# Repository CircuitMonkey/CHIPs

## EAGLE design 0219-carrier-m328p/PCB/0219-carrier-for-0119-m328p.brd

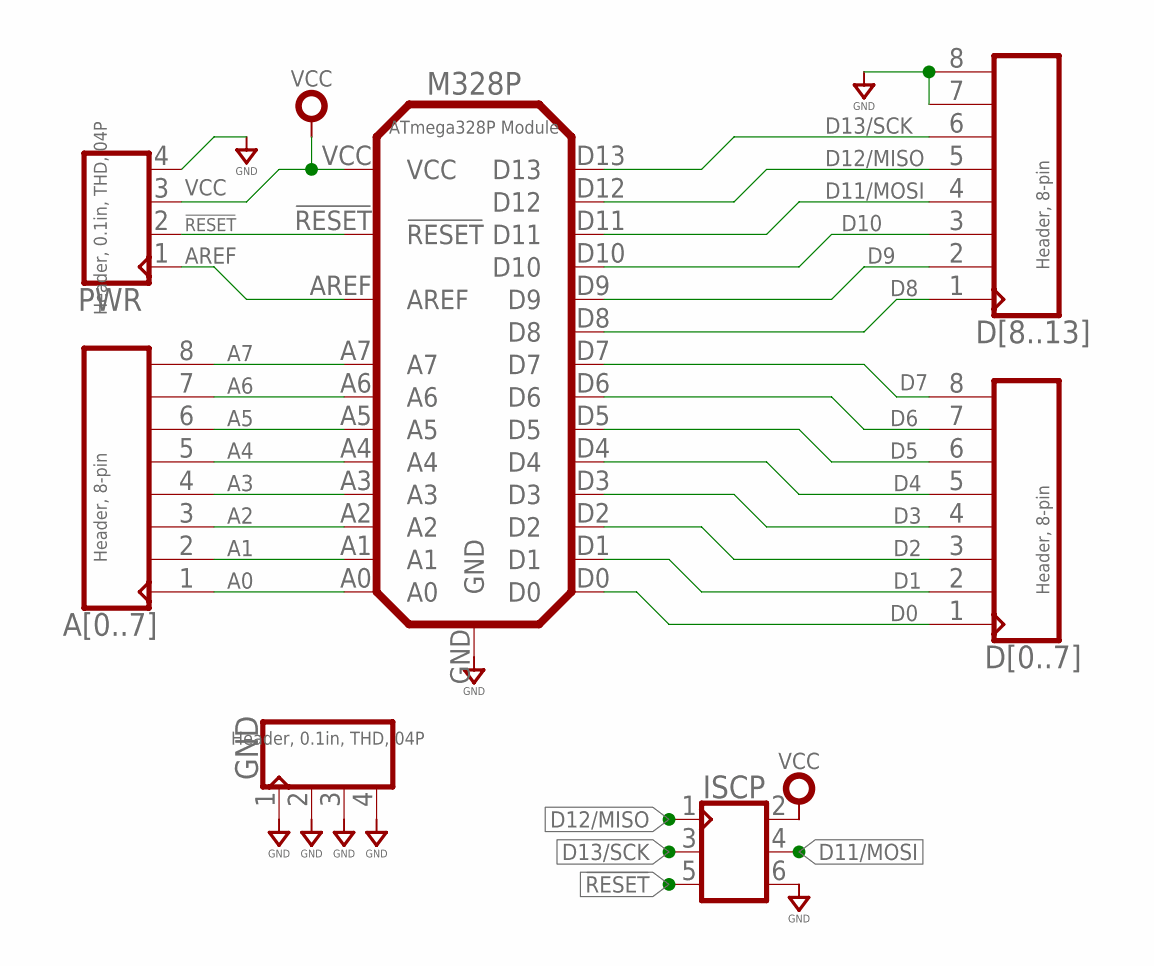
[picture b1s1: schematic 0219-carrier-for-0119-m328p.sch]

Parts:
A[0..7]: Header, 8-pin; MA08X1-VT-THD
D[0..7], D[8..13]: Header, 8-pin; MA08X1-VT-THD
GND: Header, 0.1in, THD, 04P; MA04X1-VT-THD
ISCP: CON_03X2-VT_SMD; MA03X2-VT-SMD
M328P: ATmega328P Module; 0119A
PWR: Header, 0.1in, THD, 04P; MA04X1-VT-THD

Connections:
!RESET: ISCP.5, M328P.!RESET, PWR.2
A0: A[0..7].1, M328P.A0
A1: A[0..7].2, M328P.A1
A2: A[0..7].3, M328P.A2
A3: A[0..7].4, M328P.A3
A4: A[0..7].5, M328P.A4
A5: A[0..7].6, M328P.A5
A6: A[0..7].7, M328P.A6
A7: A[0..7].8, M328P.A7
AREF: M328P.AREF, PWR.1
D0: D[0..7].1, M328P.D0
D1: D[0..7].2, M328P.D1
D2: D[0..7].3, M328P.D2
D3: D[0..7].4, M328P.D3
D4: D[0..7].5, M328P.D4
D5: D[0..7].6, M328P.D5
D6: D[0..7].7, M328P.D6
D7: D[0..7].8, M328P.D7
D8: D[8..13].1, M328P.D8
D9: D[8..13].2, M328P.D9
D10: D[8..13].3, M328P.D10
D11/MOSI: D[8..13].4, ISCP.4, M328P.D11
D12/MISO: D[8..13].5, ISCP.1, M328P.D12
D13/SCK: D[8..13].6, ISCP.3, M328P.D13
GND: D[8..13].7, D[8..13].8, GND.1, GND.2, GND.3, GND.4, ISCP.6, M328P.GND, PWR.4
VCC: ISCP.2, M328P.VCC, PWR.3

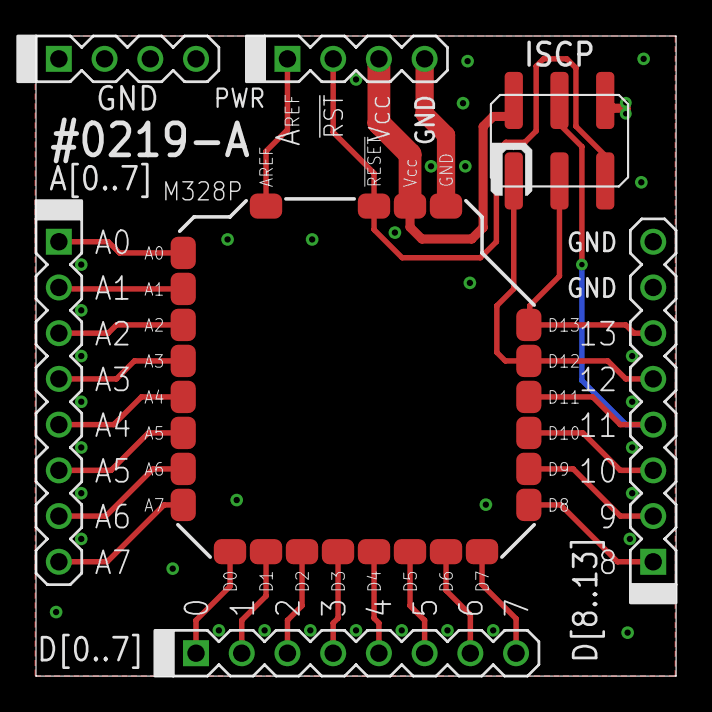
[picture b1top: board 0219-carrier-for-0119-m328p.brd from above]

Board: 2 copper layers, 35.6 x 35.6 mm, 7 parts (0 on the bottom side), 26 nets.

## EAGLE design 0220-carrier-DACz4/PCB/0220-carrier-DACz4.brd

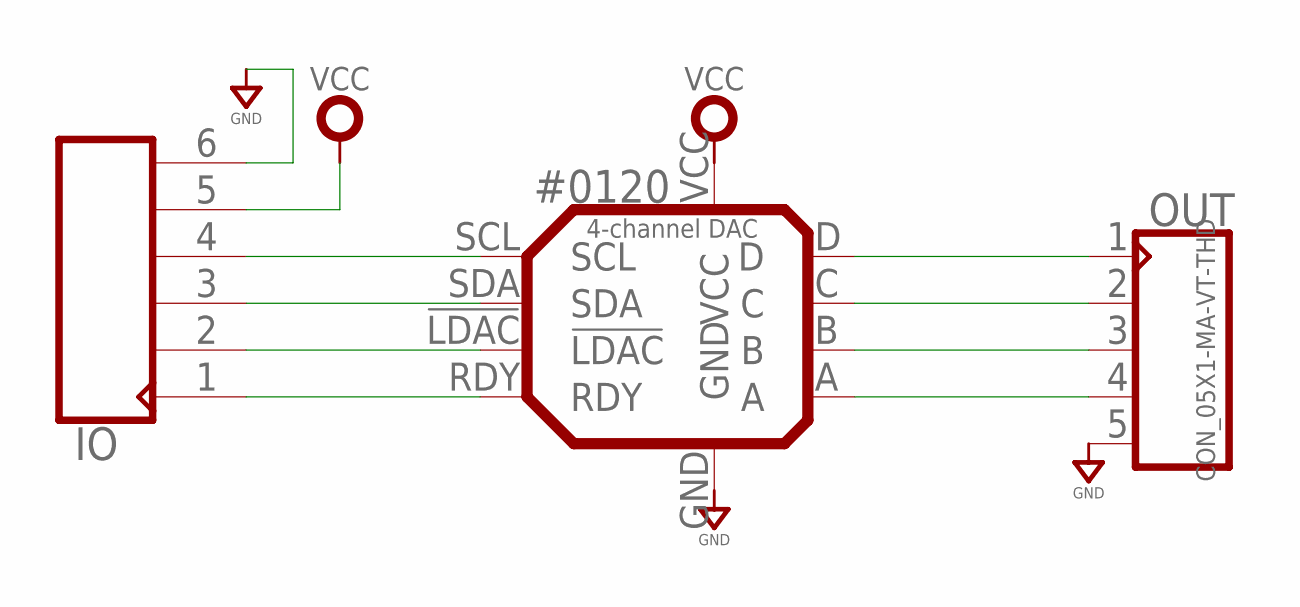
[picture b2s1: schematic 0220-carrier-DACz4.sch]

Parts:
#0120: 4-channel DAC; 0120A
IO: CON_06X1-VT; MA06X1-VT-THD
OUT: CON_05X1-MA-VT-THD; MA05X1-VT-THD

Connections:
GND: #0120.GND, IO.6, OUT.5
unnamed: #0120.RDY, IO.1
unnamed: #0120.!LDAC, IO.2
unnamed: #0120.SDA, IO.3
unnamed: #0120.SCL, IO.4
unnamed: #0120.A, OUT.4
unnamed: #0120.B, OUT.3
unnamed: #0120.C, OUT.2
unnamed: #0120.D, OUT.1
VCC: #0120.VCC, IO.5

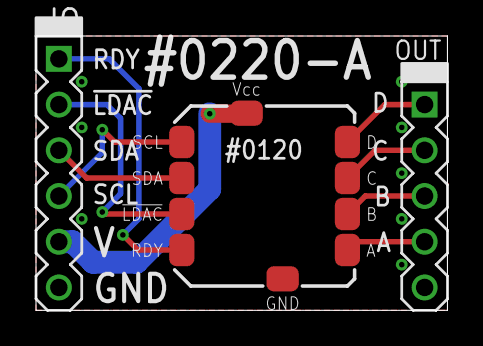
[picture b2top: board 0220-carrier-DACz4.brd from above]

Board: 2 copper layers, 22.9 x 15.2 mm, 3 parts (0 on the bottom side), 10 nets.

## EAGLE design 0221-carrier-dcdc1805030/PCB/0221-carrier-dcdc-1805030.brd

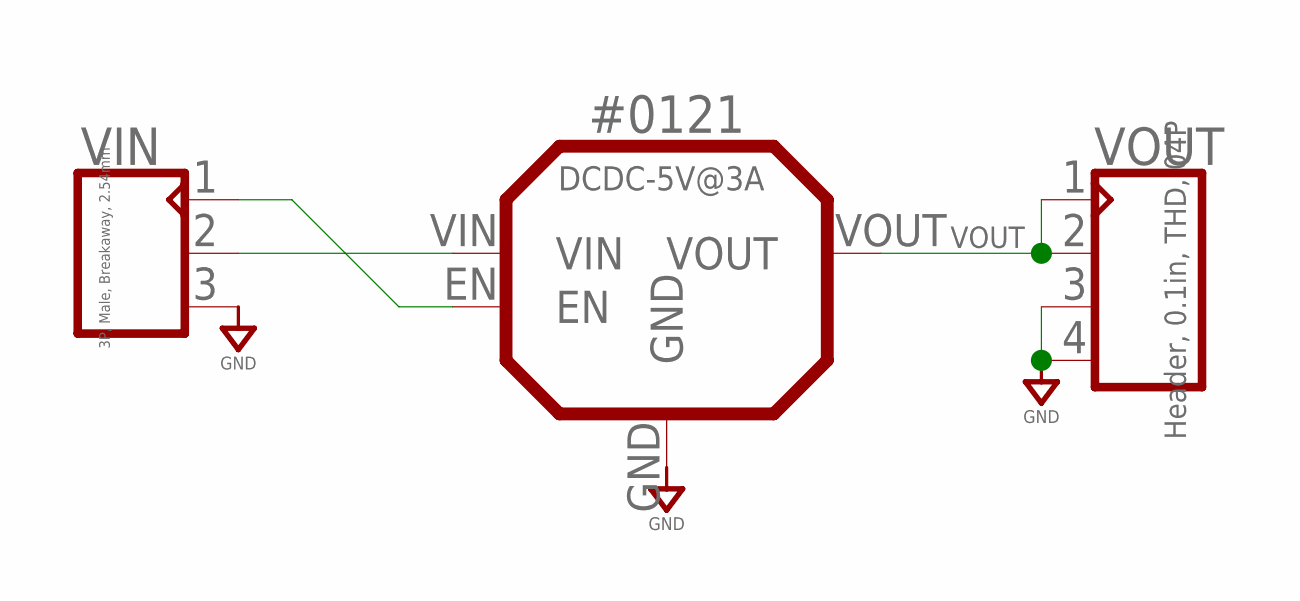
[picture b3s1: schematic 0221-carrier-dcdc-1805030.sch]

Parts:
#0121: DCDC-5V@3A; 0121A
VIN: 3P, Male, Breakaway, 2.54mm; MA03X1-VT-THD
VOUT: Header, 0.1in, THD, 04P; MA04X1-VT-THD

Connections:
GND: #0121.GND, VIN.3, VOUT.3, VOUT.4
unnamed: #0121.VIN, VIN.2
unnamed: #0121.EN, VIN.1
VOUT: #0121.VOUT, VOUT.1, VOUT.2

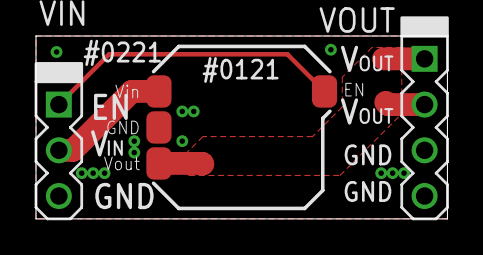
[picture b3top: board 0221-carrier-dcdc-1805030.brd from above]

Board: 2 copper layers, 22.9 x 10.2 mm, 3 parts (0 on the bottom side), 4 nets.

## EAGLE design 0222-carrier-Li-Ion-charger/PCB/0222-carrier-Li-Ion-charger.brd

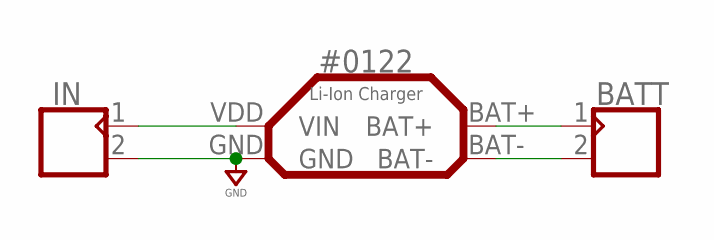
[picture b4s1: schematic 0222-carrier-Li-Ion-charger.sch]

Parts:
#0122: Li-Ion Charger; 0122A
BATT: CON_02X1-2.54MM-THD-VT; MA02X1-VT-THD
IN: CON_02X1-2.54MM-THD-VT; MA02X1-VT-THD

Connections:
GND: #0122.GND, IN.2
unnamed: #0122.VDD (VIN), IN.1
unnamed: #0122.BAT-, BATT.2
unnamed: #0122.BAT+, BATT.1

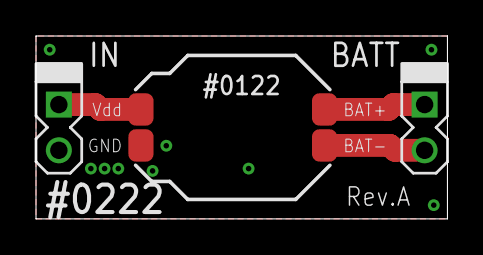
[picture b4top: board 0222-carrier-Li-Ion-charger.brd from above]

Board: 2 copper layers, 22.9 x 10.2 mm, 3 parts (0 on the bottom side), 4 nets.

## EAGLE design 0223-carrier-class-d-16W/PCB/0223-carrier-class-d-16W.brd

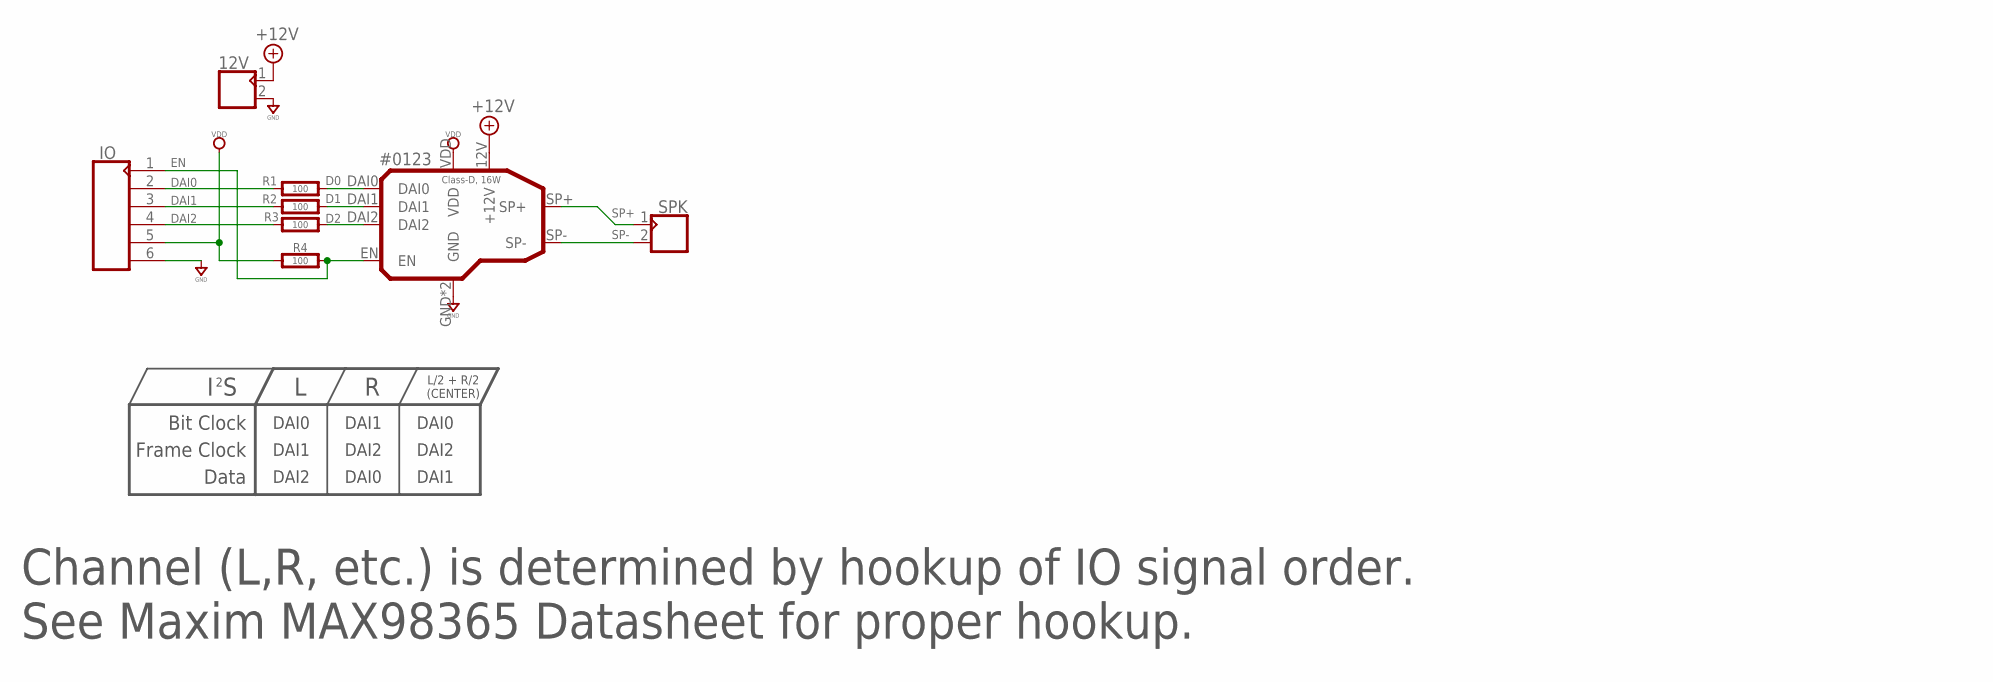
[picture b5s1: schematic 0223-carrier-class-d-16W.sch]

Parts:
12V: CON_02X1-2.54MM-THD-VT; MA02X1-VT-THD
#0123: Class-D, 16W; 0123A
IO: CON_06X1-VT; MA06X1-VT-THD
R1, R2, R3, R4: 100; 0603-RES
SPK: CON_02X1-2.54MM-THD-VT; MA02X1-VT-THD

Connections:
+12V: 12V.1, #0123.12V (+12V)
D0: #0123.DAI0, R1.2
D1: #0123.DAI1, R2.2
D2: #0123.DAI2, R3.2
DAI0: IO.2, R1.1
DAI1: IO.3, R2.1
DAI2: IO.4, R3.1
EN: #0123.EN, IO.1, R4.2
GND: 12V.2, #0123.GND, #0123.GND2 (GND), IO.6
SP+: #0123.SP+, SPK.1
SP-: #0123.SP-, SPK.2
VDD: #0123.VDD, IO.5, R4.1

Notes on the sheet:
Channel (L,R, etc.) is determined by hookup of IO signal order. See Maxim MAX98365 Datasheet for proper hookup.
Bit Clock
Frame Clock
Data
L/2 + R/2 (CENTER)
DAI0
DAI1
DAI2

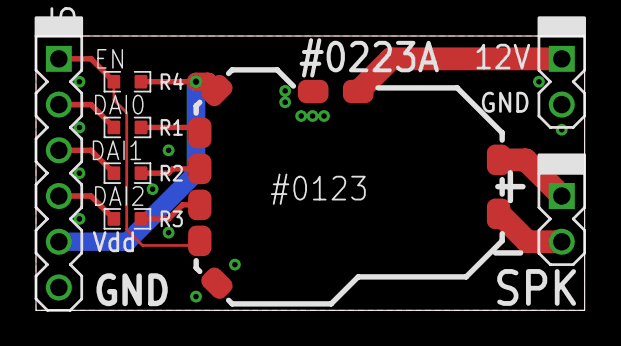
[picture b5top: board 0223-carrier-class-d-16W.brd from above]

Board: 2 copper layers, 30.5 x 15.2 mm, 8 parts (0 on the bottom side), 12 nets.

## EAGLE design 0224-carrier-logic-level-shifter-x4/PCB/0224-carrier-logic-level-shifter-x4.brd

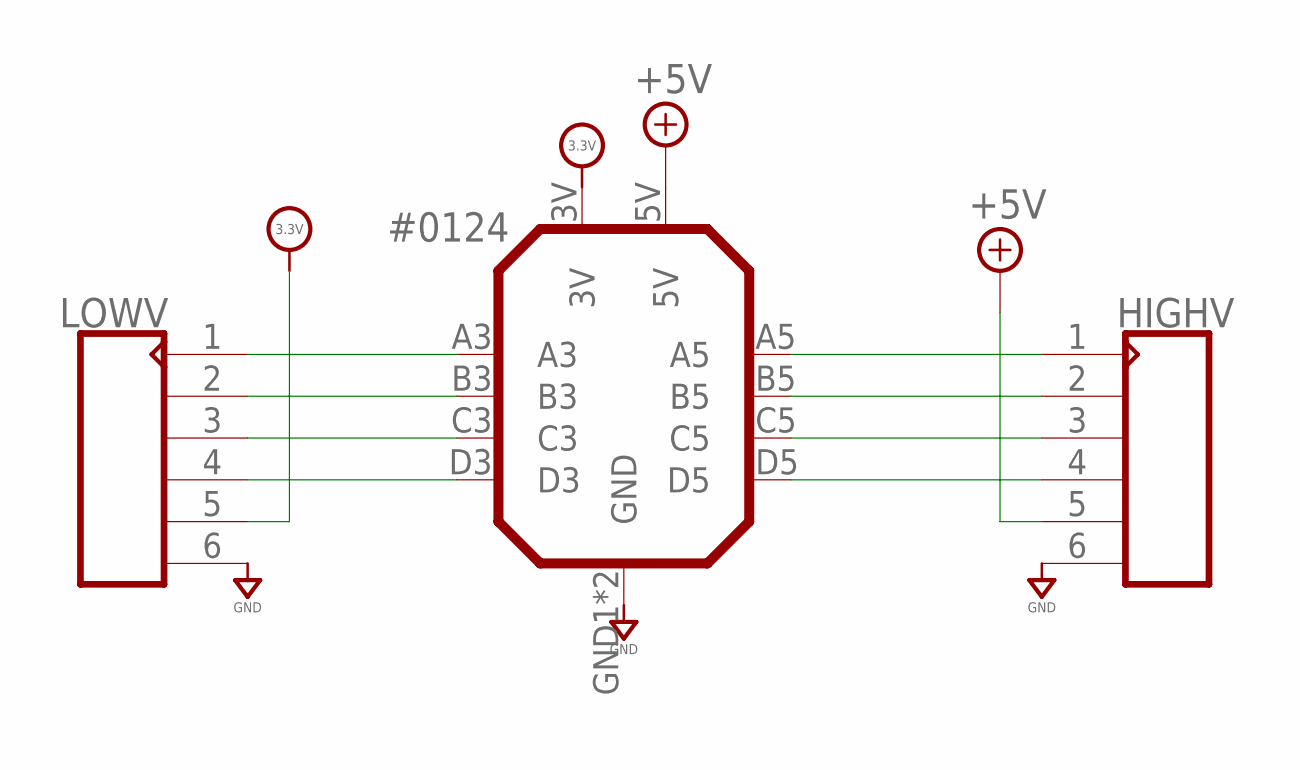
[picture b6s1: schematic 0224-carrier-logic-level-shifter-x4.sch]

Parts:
#0124: 0124REV-A; 0124A
HIGHV: CON_06X1-VT; MA06X1-VT-THD
LOWV: CON_06X1-VT; MA06X1-VT-THD

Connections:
+3.3V: #0124.3V, LOWV.5
+5V: #0124.5V, HIGHV.5
GND: #0124.GND1 (GND), #0124.GND2 (GND), HIGHV.6, LOWV.6
unnamed: #0124.D3, LOWV.4
unnamed: #0124.C3, LOWV.3
unnamed: #0124.B3, LOWV.2
unnamed: #0124.A3, LOWV.1
unnamed: #0124.D5, HIGHV.4
unnamed: #0124.C5, HIGHV.3
unnamed: #0124.B5, HIGHV.2
unnamed: #0124.A5, HIGHV.1

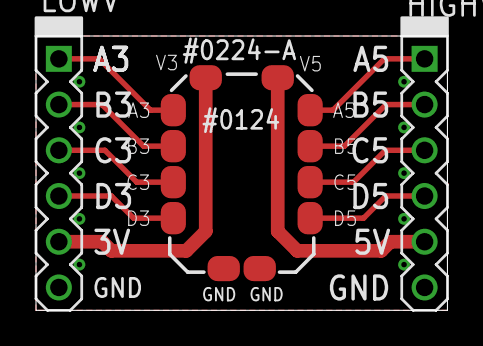
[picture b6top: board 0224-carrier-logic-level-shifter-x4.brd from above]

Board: 2 copper layers, 22.9 x 15.2 mm, 3 parts (0 on the bottom side), 11 nets.
